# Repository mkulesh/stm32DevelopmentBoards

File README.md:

#  "Development boards and software templates for STM32 MCU"

This repository contains schematic of development boards, PCB, and C++ source code templates that can be helpful for development using STM32 micro-controllers. It provides small, universal, and breadboards-friendly adapter and development board for wide range of STM32 controllers.  There are three sets:

## STM32-Pi Board

The first board is a two-layers STM32F4 board, which have a form-factor of Raspberry Pi B+ that allows us to use any case available for this single-board computer:

If you like to test this board, you can order it [on DirtyPCBs.com](http://dirtypcbs.com/store/designer/details/9348/6105/stm32-pi-board-v1-3-zip)

### Specification
* It is based on high-performance ARM®Cortex®-M4 32-bit RISC micro-controller [STM32F405RG](http://www.st.com/en/microcontrollers/stm32f405rg.html)
* SMD HSE and LSE crystals
* Micro SD Card Connector
* Mini USB Type B Connector with USB EMI filtering and ESD protection. This connector can be used for data transfer and powering
* A separate +5V DC connector (1 mm X 3.2 mm) instead of Raspberry Pi audio jack
* 6-pin SWD connector used to program the MCU
* [ESP8266](https://en.wikipedia.org/wiki/ESP8266) WiFi Module ESP-11 instead of Raspberry Pi network connector
* 5-pin connector used to flash and program the ESP-11 module
* Breadboard-compatible 1x20-pin and 1x10-pin headers connected to free MCU pins
* Reset button
* One RGB LED
* Low power audio DAC with PLL UDA1334ATS
* 2x class-D mono audio power amplifier IS31AP2005 (2 x 2.95W) 
* 4 pads for audio output instead of Raspberry Pi USB connector
* SMD size for passive components is 0805

### Documentation
* [Отладочная плата STM32F4 в форм-факторе Raspberry Pi (In Russian)](https://habr.com/post/413101)
* [Schematic](https://docs.google.com/viewer?url=https://github.com/mkulesh/stm32DevelopmentBoards/raw/master/pcb/stm32_pi_board_sch.pdf) 
* [Dimensions](https://docs.google.com/viewer?url=https://github.com/mkulesh/stm32DevelopmentBoards/raw/master/pcb/stm32_pi_board_mech.pdf) 
* [Top layer](https://docs.google.com/viewer?url=https://github.com/mkulesh/stm32DevelopmentBoards/raw/master/pcb/stm32_pi_board_top.pdf)
* [Bottom layer](https://docs.google.com/viewer?url=https://github.com/mkulesh/stm32DevelopmentBoards/raw/master/pcb/stm32_pi_board_bottom.pdf) 
* [Bill of materials](http://htmlpreview.github.io/?https://github.com/mkulesh/stm32DevelopmentBoards/blob/master/pcb/stm32_pi_board_bom.html)
* The C++ example in the directory [src/PI405RG](https://github.com/mkulesh/stm32DevelopmentBoards/tree/master/src/PI405RG) demonstrates how to use RTC, SD Card with FatFS, and ESP-11 module.

## Universal STM32 Boards:

These developments boards are two-side breadboard adapters for LQFP32/48/64 IC's, equipment with adaptable power supply circuit, HSE and LSE crystal circuit, reset button, and a **custom** 10-pin JTAG connector. SMD size for passive components is 0805. 

The adapter between 20-pin JTAG and this custom connector is also included in the set:

You can order these boards [on DirtyPCBs.com](http://dirtypcbs.com/store/designer/details/9348/5771/stm32-development-boards)

## LQFP-Breadboard Adapters:

These boards are just one-side breadboard adapters for LQFP32/48/64 IC's:

You can order these boards [on DirtyPCBs.com](http://dirtypcbs.com/store/designer/details/9348/5770/lqfp-adapters-zip)

## Repository Content:

* The directory **pcb** contains schematic and board layout developed in [Eagle CAD](https://www.autodesk.com/products/eagle/free-download)
* In the directory **images**, you can find some photos of assembled boards
* The directory **src** contains test examples developed in [System Workbench for STM32](http://www.st.com/en/development-tools/sw4stm32.html). These test programs are based on HAL library and an object-oriented abstraction layer called *StmPlusPlus*. Currently, following chips are tested: STM32F303K8Tx, STM32F303RBTx, STM32F373CBTx, STM32F373CCTx, STM32F410RBTx,  STM32F405RGTx

## Reviews and Publications:
* [Discussion on www.mikrocontroller.net (In German)](https://www.mikrocontroller.net/topic/433910)
* [Нестандартный способ подружиться с STM32: не Ардуино и не Discovery (In Russian)](https://habr.com/post/406313)

## License
This software is published under the *GNU General Public License, Version 3*

Copyright (C) 2014-2017 Mikhail Kulesh

This program is free software: you can redistribute it and/or modify it under the terms of the GNU General Public License as published by the Free Software Foundation, either version 3 of the License, or (at your option) any later version.

This program is distributed in the hope that it will be useful, but WITHOUT ANY WARRANTY; without even the implied warranty of MERCHANTABILITY or FITNESS FOR A PARTICULAR PURPOSE.  See the GNU General Public License for more details. You should have received a copy of the GNU General Public License along with this program.

If not, see [www.gnu.org/licenses](http://www.gnu.org/licenses).

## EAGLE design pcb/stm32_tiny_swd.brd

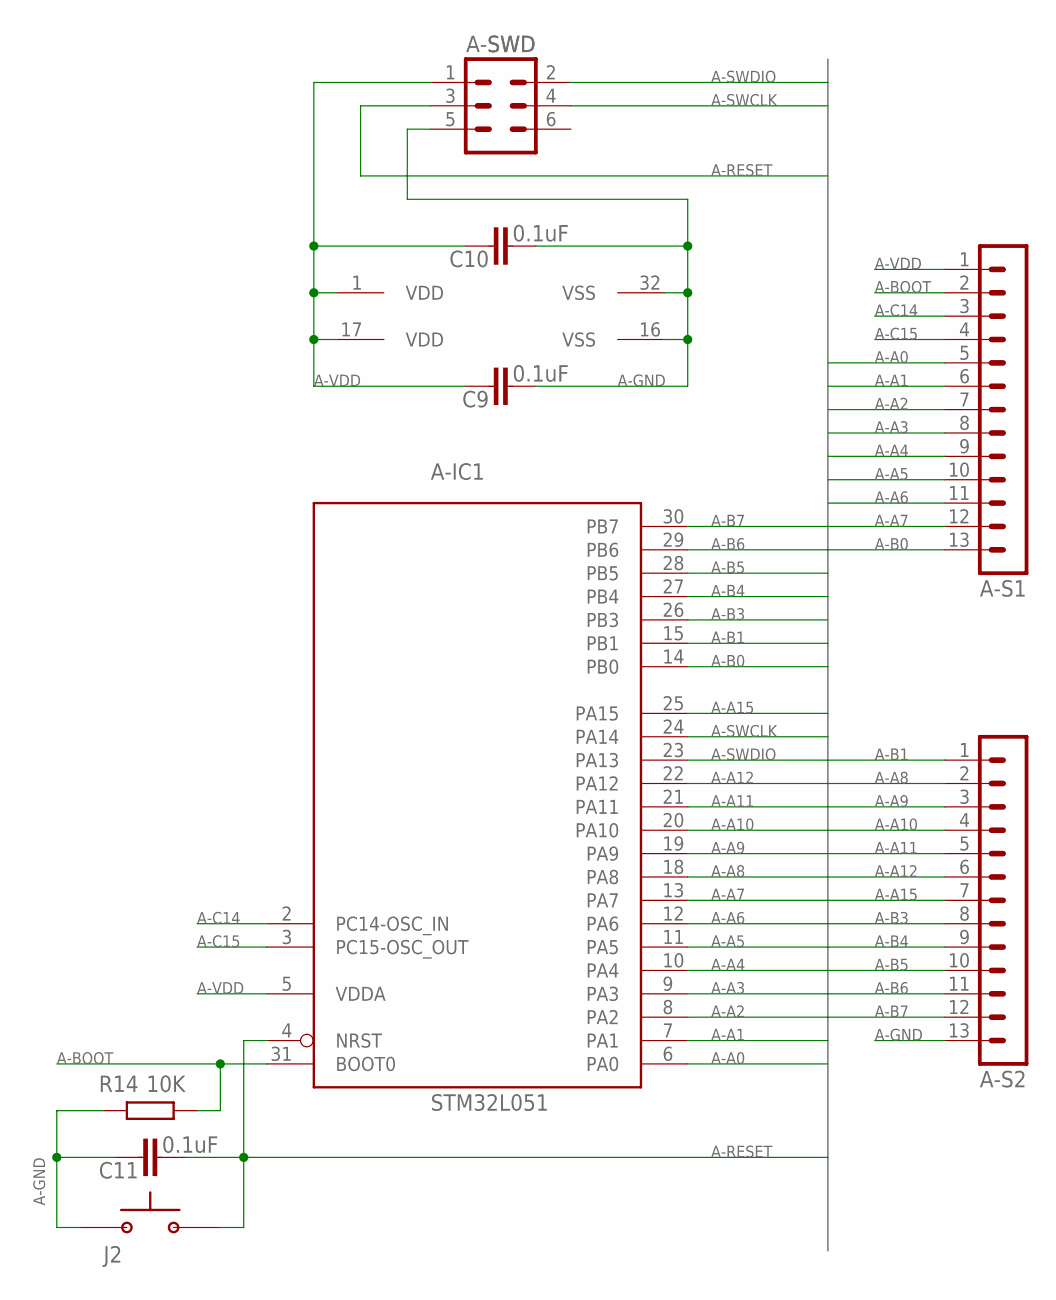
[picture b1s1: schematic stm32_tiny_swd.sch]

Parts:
A-IC1: STM32L051; LQFP32
A-S1, A-S2: MA13-1
A-SWD: SWD; MA03-2
C9, C10, C11: 0.1uF; C0805
J2: BUTTON-FSM14JRT
R14: 10K; R0805

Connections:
A-A0: A-IC1.6 (PA0), A-S1.5
A-A1: A-IC1.7 (PA1), A-S1.6
A-A2: A-IC1.8 (PA2), A-S1.7
A-A3: A-IC1.9 (PA3), A-S1.8
A-A4: A-IC1.10 (PA4), A-S1.9
A-A5: A-IC1.11 (PA5), A-S1.10
A-A6: A-IC1.12 (PA6), A-S1.11
A-A7: A-IC1.13 (PA7), A-S1.12
A-A8: A-IC1.18 (PA8), A-S2.2
A-A9: A-IC1.19 (PA9), A-S2.3
A-A10: A-IC1.20 (PA10), A-S2.4
A-A11: A-IC1.21 (PA11), A-S2.5
A-A12: A-IC1.22 (PA12), A-S2.6
A-A15: A-IC1.25 (PA15), A-S2.7
A-B0: A-IC1.14 (PB0), A-S1.13
A-B1: A-IC1.15 (PB1), A-S2.1
A-B3: A-IC1.26 (PB3), A-S2.8
A-B4: A-IC1.27 (PB4), A-S2.9
A-B5: A-IC1.28 (PB5), A-S2.10
A-B6: A-IC1.29 (PB6), A-S2.11
A-B7: A-IC1.30 (PB7), A-S2.12
A-BOOT: A-IC1.31 (BOOT0), A-S1.2, R14.1
A-C14: A-IC1.2 (PC14-OSC_IN), A-S1.3
A-C15: A-IC1.3 (PC15-OSC_OUT), A-S1.4
A-GND: A-IC1.16 (VSS), A-IC1.32 (VSS), A-S2.13, A-SWD.5, C9.2, C10.2, C11.1, J2.P$1 (1), R14.2
A-RESET: A-IC1.4 (NRST), A-SWD.3, C11.2, J2.P$2 (2)
A-SWCLK: A-IC1.24 (PA14), A-SWD.4
A-SWDIO: A-IC1.23 (PA13), A-SWD.2
A-VDD: A-IC1.1 (VDD), A-IC1.5 (VDDA), A-IC1.17 (VDD), A-S1.1, A-SWD.1, C9.1, C10.1

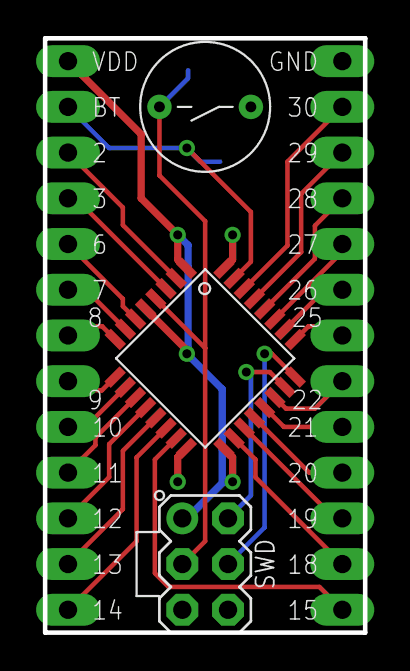
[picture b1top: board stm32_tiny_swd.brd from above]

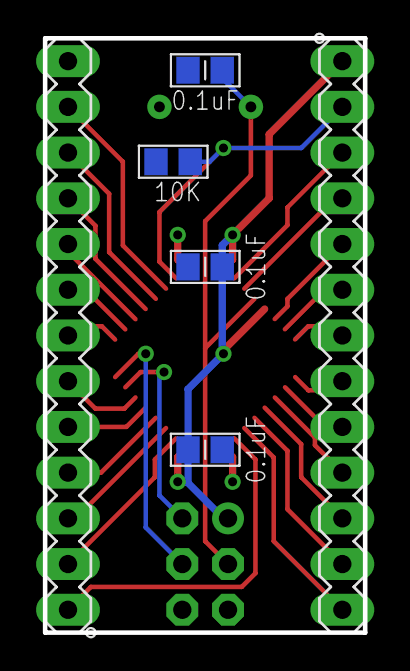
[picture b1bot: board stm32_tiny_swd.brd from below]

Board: 2 copper layers, 17.8 x 33.0 mm, 9 parts (6 on the bottom side), 29 nets.

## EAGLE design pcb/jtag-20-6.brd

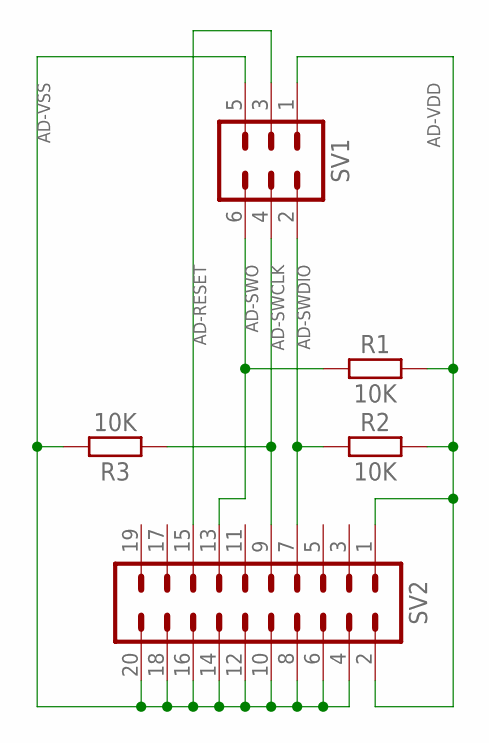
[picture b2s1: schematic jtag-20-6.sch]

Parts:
R1, R2, R3: 10K; R1206
SV1: MA03-2
SV2: MA10-2

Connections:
AD-RESET: SV1.3, SV2.15
AD-SWCLK: R3.1, SV1.4, SV2.9
AD-SWDIO: R2.1, SV1.2, SV2.7
AD-SWO: R1.1, SV1.6, SV2.13
AD-VDD: R1.2, R2.2, SV1.1, SV2.1, SV2.2
AD-VSS: R3.2, SV1.5, SV2.4, SV2.6, SV2.8, SV2.10, SV2.12, SV2.14, SV2.16, SV2.18, SV2.20

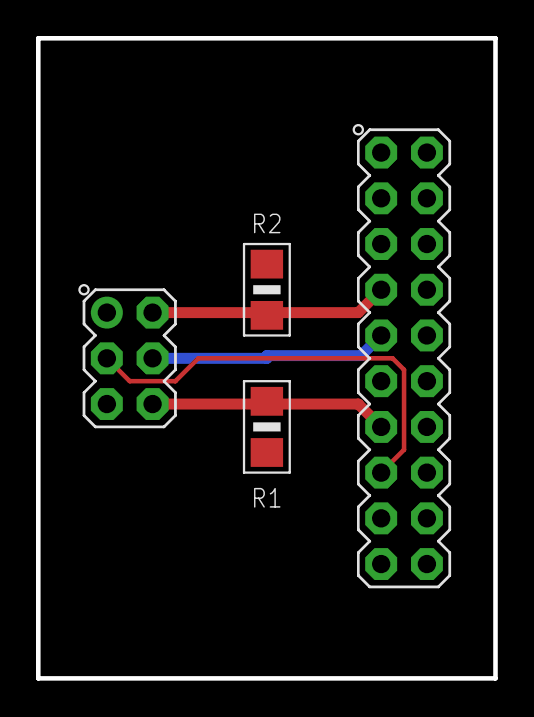
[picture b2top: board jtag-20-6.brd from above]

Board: 2 copper layers, 25.4 x 35.6 mm, 5 parts (1 on the bottom side), 6 nets.

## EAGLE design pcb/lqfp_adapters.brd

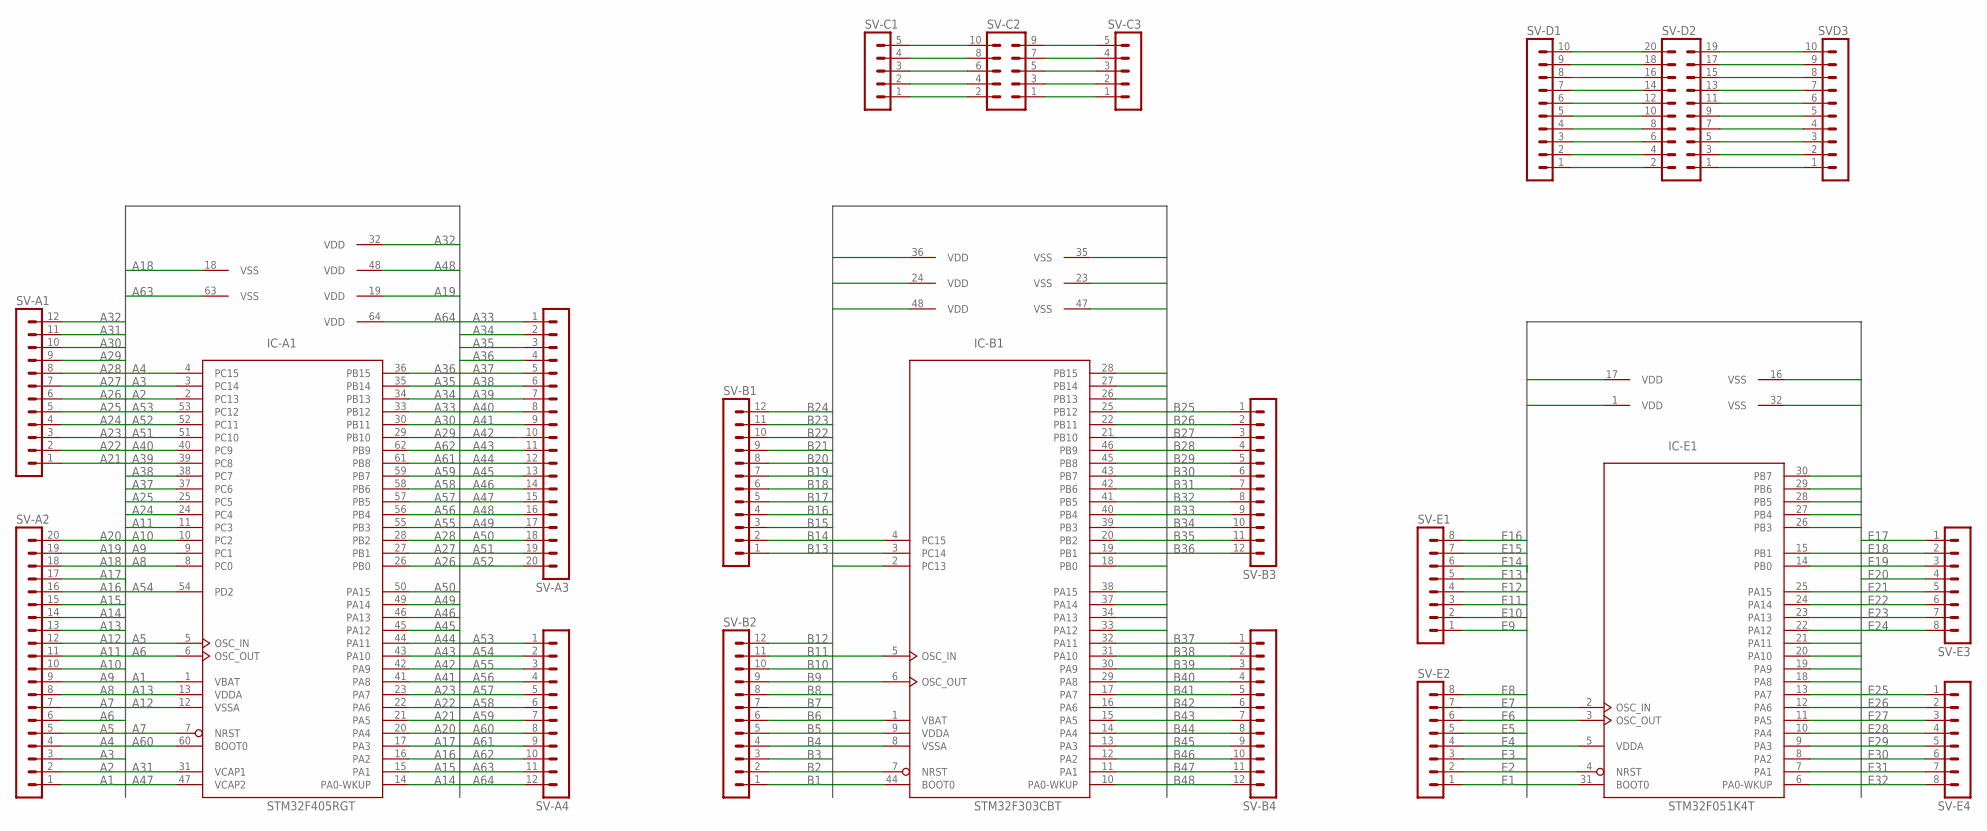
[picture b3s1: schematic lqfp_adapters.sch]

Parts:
IC-A1: STM32F405RGT; LQFP64
IC-B1: STM32F303CBT; LQFP48
IC-E1: STM32F051K4T; LQFP32
SV-A1, SV-A4: MA12-1NO-PL; MA12-1-NO-PL
SV-A2, SV-A3: MA20-1NO-PL; MA20-1-NO-PL
SV-B1, SV-B2, SV-B3, SV-B4: MA12-1NO-PL; MA12-1-NO-PL
SV-C1, SV-C3: MA05-1NO-PL; MA05-1-NO-PL
SV-C2: MA05-2
SV-D1: MA10-1NO-PL; MA10-1-NO-PL
SV-D2: MA10-2
SV-E1, SV-E2, SV-E3, SV-E4: MA08-1NO-PL; MA08-1-NO-PL
SVD3: MA10-1NO-PL; MA10-1-NO-PL

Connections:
A1: IC-A1.1 (VBAT), SV-A2.1
A2: IC-A1.2 (PC13), SV-A2.2
A3: IC-A1.3 (PC14), SV-A2.3
A4: IC-A1.4 (PC15), SV-A2.4
A5: IC-A1.5 (OSC_IN), SV-A2.5
A6: IC-A1.6 (OSC_OUT), SV-A2.6
A7: IC-A1.7 (NRST), SV-A2.7
A8: IC-A1.8 (PC0), SV-A2.8
A9: IC-A1.9 (PC1), SV-A2.9
A10: IC-A1.10 (PC2), SV-A2.10
A11: IC-A1.11 (PC3), SV-A2.11
A12: IC-A1.12 (VSSA), SV-A2.12
A13: IC-A1.13 (VDDA), SV-A2.13
A14: IC-A1.14 (PA0-WKUP), SV-A2.14
A15: IC-A1.15 (PA1), SV-A2.15
A16: IC-A1.16 (PA2), SV-A2.16
A17: IC-A1.17 (PA3), SV-A2.17
A18: IC-A1.18 (VSS), SV-A2.18
A19: IC-A1.19 (VDD), SV-A2.19
A20: IC-A1.20 (PA4), SV-A2.20
A21: IC-A1.21 (PA5), SV-A1.1
A22: IC-A1.22 (PA6), SV-A1.2
A23: IC-A1.23 (PA7), SV-A1.3
A24: IC-A1.24 (PC4), SV-A1.4
A25: IC-A1.25 (PC5), SV-A1.5
A26: IC-A1.26 (PB0), SV-A1.6
A27: IC-A1.27 (PB1), SV-A1.7
A28: IC-A1.28 (PB2), SV-A1.8
A29: IC-A1.29 (PB10), SV-A1.9
A30: IC-A1.30 (PB11), SV-A1.10
A31: IC-A1.31 (VCAP1), SV-A1.11
A32: IC-A1.32 (VDD), SV-A1.12
A33: IC-A1.33 (PB12), SV-A3.1
A34: IC-A1.34 (PB13), SV-A3.2
A35: IC-A1.35 (PB14), SV-A3.3
A36: IC-A1.36 (PB15), SV-A3.4
A37: IC-A1.37 (PC6), SV-A3.5
A38: IC-A1.38 (PC7), SV-A3.6
A39: IC-A1.39 (PC8), SV-A3.7
A40: IC-A1.40 (PC9), SV-A3.8
A41: IC-A1.41 (PA8), SV-A3.9
A42: IC-A1.42 (PA9), SV-A3.10
A43: IC-A1.43 (PA10), SV-A3.11
A44: IC-A1.44 (PA11), SV-A3.12
A45: IC-A1.45 (PA12), SV-A3.13
A46: IC-A1.46 (PA13), SV-A3.14
A47: IC-A1.47 (VCAP2), SV-A3.15
A48: IC-A1.48 (VDD), SV-A3.16
A49: IC-A1.49 (PA14), SV-A3.17
A50: IC-A1.50 (PA15), SV-A3.18
A51: IC-A1.51 (PC10), SV-A3.19
A52: IC-A1.52 (PC11), SV-A3.20
A53: IC-A1.53 (PC12), SV-A4.1
A54: IC-A1.54 (PD2), SV-A4.2
A55: IC-A1.55 (PB3), SV-A4.3
A56: IC-A1.56 (PB4), SV-A4.4
A57: IC-A1.57 (PB5), SV-A4.5
A58: IC-A1.58 (PB6), SV-A4.6
A59: IC-A1.59 (PB7), SV-A4.7
A60: IC-A1.60 (BOOT0), SV-A4.8
A61: IC-A1.61 (PB8), SV-A4.9
A62: IC-A1.62 (PB9), SV-A4.10
A63: IC-A1.63 (VSS), SV-A4.11
A64: IC-A1.64 (VDD), SV-A4.12
B1: IC-B1.1 (VBAT), SV-B2.1
B2: IC-B1.2 (PC13), SV-B2.2
B3: IC-B1.3 (PC14), SV-B2.3
B4: IC-B1.4 (PC15), SV-B2.4
B5: IC-B1.5 (OSC_IN), SV-B2.5
B6: IC-B1.6 (OSC_OUT), SV-B2.6
B7: IC-B1.7 (NRST), SV-B2.7
B8: IC-B1.8 (VSSA), SV-B2.8
B9: IC-B1.9 (VDDA), SV-B2.9
B10: IC-B1.10 (PA0-WKUP), SV-B2.10
B11: IC-B1.11 (PA1), SV-B2.11
B12: IC-B1.12 (PA2), SV-B2.12
B13: IC-B1.13 (PA3), SV-B1.1
B14: IC-B1.14 (PA4), SV-B1.2
B15: IC-B1.15 (PA5), SV-B1.3
B16: IC-B1.16 (PA6), SV-B1.4
B17: IC-B1.17 (PA7), SV-B1.5
B18: IC-B1.18 (PB0), SV-B1.6
B19: IC-B1.19 (PB1), SV-B1.7
B20: IC-B1.20 (PB2), SV-B1.8
B21: IC-B1.21 (PB10), SV-B1.9
B22: IC-B1.22 (PB11), SV-B1.10
B23: IC-B1.23 (VSS), SV-B1.11
B24: IC-B1.24 (VDD), SV-B1.12
B25: IC-B1.25 (PB12), SV-B3.1
B26: IC-B1.26 (PB13), SV-B3.2
B27: IC-B1.27 (PB14), SV-B3.3
B28: IC-B1.28 (PB15), SV-B3.4
B29: IC-B1.29 (PA8), SV-B3.5
B30: IC-B1.30 (PA9), SV-B3.6
B31: IC-B1.31 (PA10), SV-B3.7
B32: IC-B1.32 (PA11), SV-B3.8
B33: IC-B1.33 (PA12), SV-B3.9
B34: IC-B1.34 (PA13), SV-B3.10
B35: IC-B1.35 (VSS), SV-B3.11
B36: IC-B1.36 (VDD), SV-B3.12
B37: IC-B1.37 (PA14), SV-B4.1
B38: IC-B1.38 (PA15), SV-B4.2
B39: IC-B1.39 (PB3), SV-B4.3
B40: IC-B1.40 (PB4), SV-B4.4
B41: IC-B1.41 (PB5), SV-B4.5
B42: IC-B1.42 (PB6), SV-B4.6
B43: IC-B1.43 (PB7), SV-B4.7
B44: IC-B1.44 (BOOT0), SV-B4.8
B45: IC-B1.45 (PB8), SV-B4.9
B46: IC-B1.46 (PB9), SV-B4.10
B47: IC-B1.47 (VSS), SV-B4.11
B48: IC-B1.48 (VDD), SV-B4.12
E1: IC-E1.1 (VDD), SV-E2.1
E2: IC-E1.2 (OSC_IN), SV-E2.2
E3: IC-E1.3 (OSC_OUT), SV-E2.3
E4: IC-E1.4 (NRST), SV-E2.4
E5: IC-E1.5 (VDDA), SV-E2.5
E6: IC-E1.6 (PA0-WKUP), SV-E2.6
E7: IC-E1.7 (PA1), SV-E2.7
E8: IC-E1.8 (PA2), SV-E2.8
E9: IC-E1.9 (PA3), SV-E1.1
E10: IC-E1.10 (PA4), SV-E1.2
E11: IC-E1.11 (PA5), SV-E1.3
E12: IC-E1.12 (PA6), SV-E1.4
E13: IC-E1.13 (PA7), SV-E1.5
E14: IC-E1.14 (PB0), SV-E1.6
E15: IC-E1.15 (PB1), SV-E1.7
E16: IC-E1.16 (VSS), SV-E1.8
E17: IC-E1.17 (VDD), SV-E3.1
E18: IC-E1.18 (PA8), SV-E3.2
E19: IC-E1.19 (PA9), SV-E3.3
E20: IC-E1.20 (PA10), SV-E3.4
E21: IC-E1.21 (PA11), SV-E3.5
E22: IC-E1.22 (PA12), SV-E3.6
E23: IC-E1.23 (PA13), SV-E3.7
E24: IC-E1.24 (PA14), SV-E3.8
E25: IC-E1.25 (PA15), SV-E4.1
E26: IC-E1.26 (PB3), SV-E4.2
E27: IC-E1.27 (PB4), SV-E4.3
E28: IC-E1.28 (PB5), SV-E4.4
E29: IC-E1.29 (PB6), SV-E4.5
E30: IC-E1.30 (PB7), SV-E4.6
E31: IC-E1.31 (BOOT0), SV-E4.7
E32: IC-E1.32 (VSS), SV-E4.8
unnamed: SV-C2.1, SV-C3.1
unnamed: SV-C2.3, SV-C3.2
unnamed: SV-C2.5, SV-C3.3
unnamed: SV-C2.7, SV-C3.4
unnamed: SV-C2.9, SV-C3.5
unnamed: SV-C1.1, SV-C2.2
unnamed: SV-C1.2, SV-C2.4
unnamed: SV-C1.3, SV-C2.6
unnamed: SV-C1.4, SV-C2.8
unnamed: SV-C1.5, SV-C2.10
unnamed: SV-D2.1, SVD3.1
unnamed: SV-D2.3, SVD3.2
unnamed: SV-D2.5, SVD3.3
unnamed: SV-D2.7, SVD3.4
unnamed: SV-D2.9, SVD3.5
unnamed: SV-D2.11, SVD3.6
unnamed: SV-D2.13, SVD3.7
unnamed: SV-D2.15, SVD3.8
unnamed: SV-D2.17, SVD3.9
unnamed: SV-D2.19, SVD3.10
unnamed: SV-D1.10, SV-D2.20
unnamed: SV-D1.9, SV-D2.18
unnamed: SV-D1.8, SV-D2.16
unnamed: SV-D1.7, SV-D2.14
unnamed: SV-D1.6, SV-D2.12
unnamed: SV-D1.5, SV-D2.10
unnamed: SV-D1.4, SV-D2.8
unnamed: SV-D1.3, SV-D2.6
unnamed: SV-D1.2, SV-D2.4
unnamed: SV-D1.1, SV-D2.2

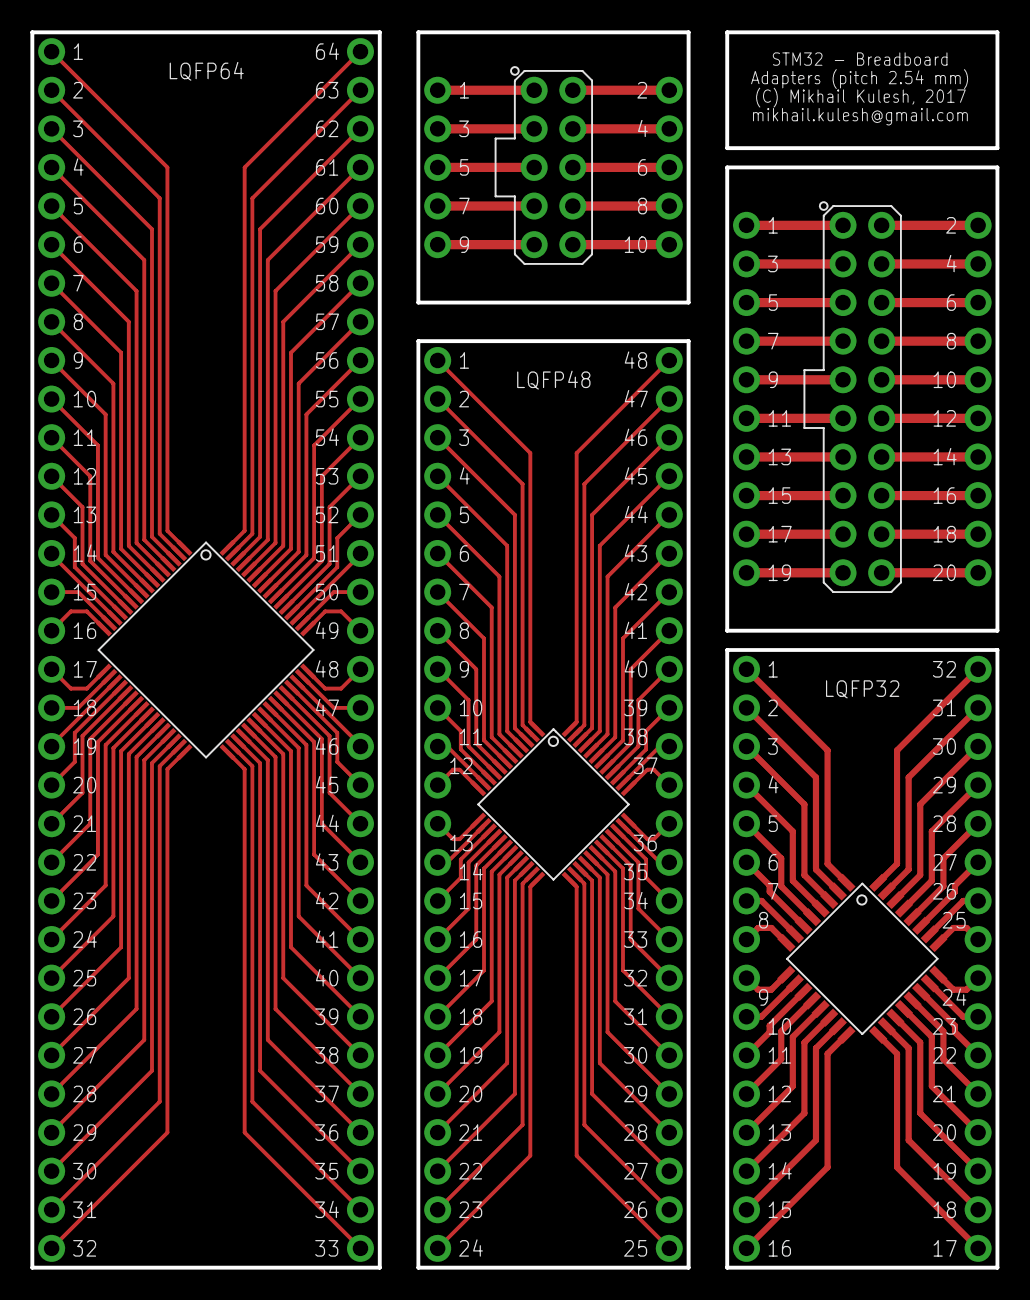
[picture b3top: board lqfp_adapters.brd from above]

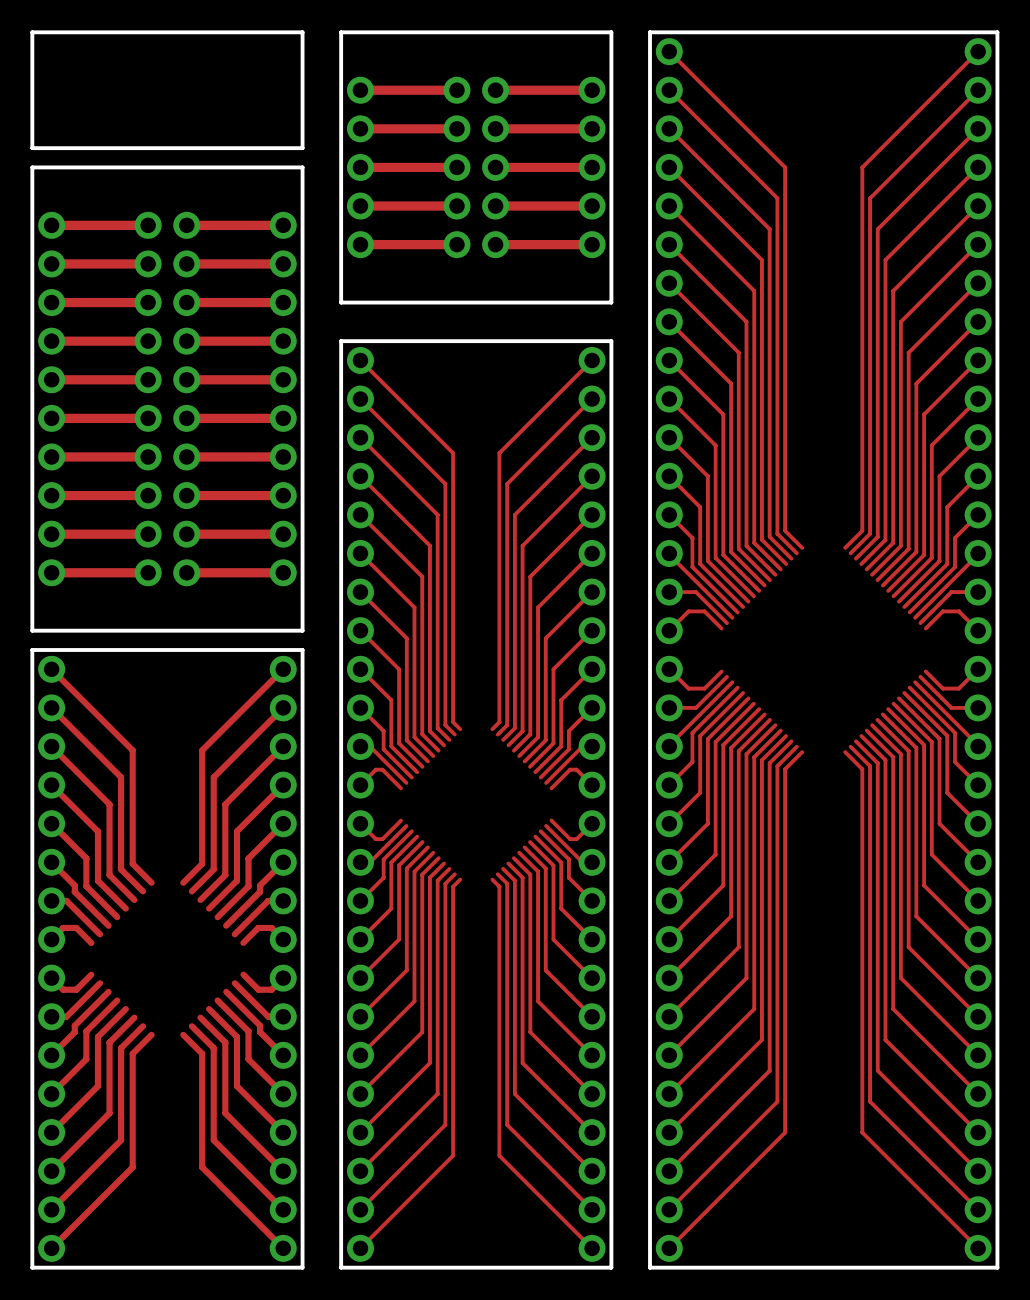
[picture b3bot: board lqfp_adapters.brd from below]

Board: 2 copper layers, 63.5 x 81.3 mm, 21 parts (16 on the bottom side), 174 nets.

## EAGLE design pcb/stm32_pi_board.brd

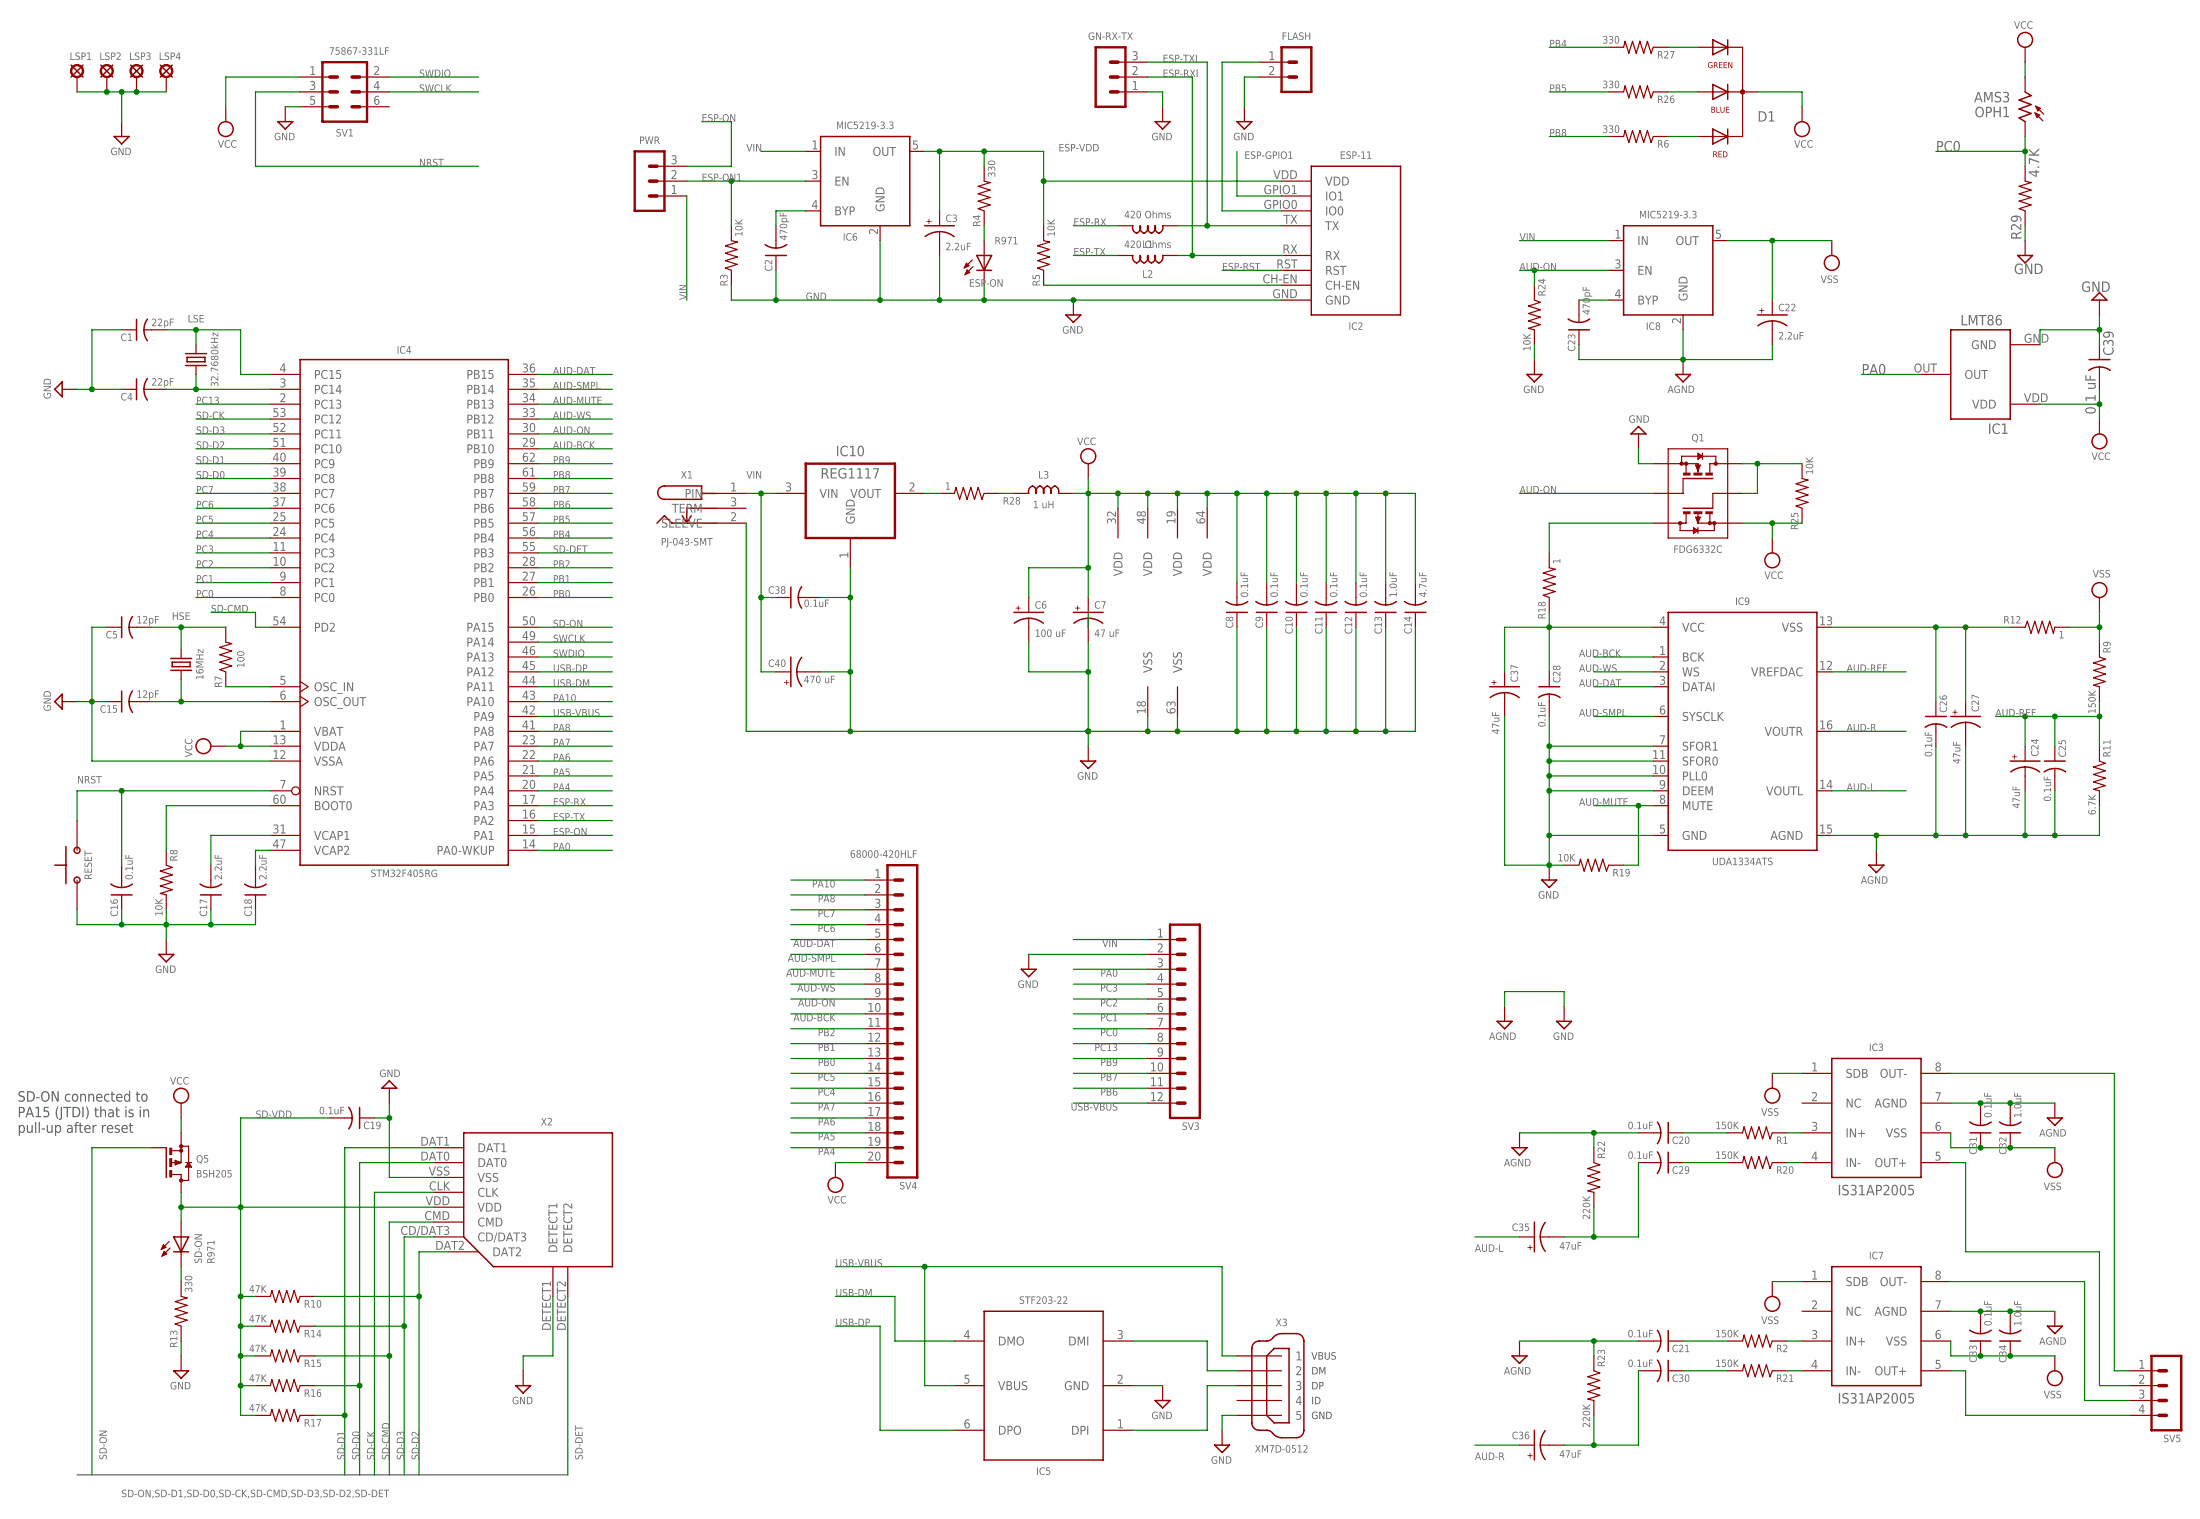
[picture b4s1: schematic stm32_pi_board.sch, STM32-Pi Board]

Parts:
C1, C4: 22pF; C0805
C2, C23: 470pF; C0805
C3, C22: 2.2uF; CPOL0805
C5, C15: 12pF; C0805
C6: 100 uF; CPOL1311
C7: 47 uF; CPOL0805
C8, C9, C10, C11, C12, C16, C19, C20, C21, C25, C26, C28, C29, C30, C31, C33, C38: 0.1uF; C0805
C13, C32, C34: 1.0uF; C0805
C14: 4.7uF; C0805
C17, C18: 2.2uF; C0805
C24, C27, C35, C36, C37: 47uF; CPOL1311
C39: 0.1 uF; C0805
C40: 470 uF; CPOL2917
D1: RGB-LED3X1MM; RGB-LED-SMD-3X1
ESP-ON: R971; CHIP-LED0805
FLASH: MA02-1
GN-RX-TX: MA03-1PL; MA03-1
HSE: 16MHz; Q-HC-46X
IC1: LMT86
IC2: ESP-11
IC3, IC7: IS31AP2005; MSOP-8
IC4: STM32F405RG; LQFP64
IC5: STF203-22; SC70-6
IC6, IC8: MIC5219-3.3; SOT23-5
IC9: UDA1334ATS; SSOP16
IC10: REG1117; SOT223
L1, L2: 420 Ohms; L0603
L3: 1 uH; L0805
LSE: 32.7680kHz; Q-CM7V-T1A
LSP1, LSP2, LSP3, LSP4: LSP27
OPH1: AMS3; VT900
PWR: MA03-1PL; MA03-1
Q1: FDG6332C; SC70-6
Q5: BSH205; SOT23
R1, R2, R9, R20, R21: 150K; R0805
R3, R5, R8, R19, R24, R25: 10K; R0805
R4, R6, R13, R26, R27: 330; R0805
R7: 100; R0805
R10, R14, R15, R16, R17: 47K; R0805
R11: 6.7K; R0805
R12, R18, R28: 1; R0805
R22, R23: 220K; R0805
R29: 4.7K; R0805
RESET: BUTTON-FSM14JRT
SD-ON: R971; CHIP-LED0805
SV1: 75867-331LF; MA03-2
SV3: MA12-1NO-PL; MA12-1-NO-PL
SV4: 68000-420HLF; MA20-1-NO-PL
SV5: MA04-1PL; MA04-1
X1: PJ-043-SMT; BUCHSE-1.0X3.2
X2: DM3AT
X3: XM7D-0512

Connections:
AUD-BCK: IC4.29 (PB10), IC9.1 (BCK), SV4.10
AUD-DAT: IC4.36 (PB15), IC9.3 (DATAI), SV4.5
AUD-L: C35.1+ (+), IC9.14 (VOUTL)
AUD-MUTE: IC4.34 (PB13), IC9.8 (MUTE), R19.1, SV4.7
AUD-ON: IC4.30 (PB11), IC8.3 (EN), Q1.2, R24.1, SV4.9
AUD-R: C36.1+ (+), IC9.16 (VOUTR)
AUD-REF: C24.1+ (+), C25.1, IC9.12 (VREFDAC), R9.2, R11.1
AUD-SMPL: IC4.35 (PB14), IC9.6 (SYSCLK), SV4.6
AUD-WS: IC4.33 (PB12), IC9.2 (WS), SV4.8
BOOT: IC4.60 (BOOT0), R8.1
ESP-GPIO1: IC2.GPIO1 (IO1)
ESP-IO0: FLASH.1, IC2.GPIO0 (IO0)
ESP-ON: IC4.15 (PA1), PWR.3
ESP-ON1: IC6.3 (EN), PWR.2, R3.2
ESP-RST: IC2.RST
ESP-RX: IC4.17 (PA3), L1.2
ESP-RXI: GN-RX-TX.2, IC2.RX, L2.1
ESP-TX: IC4.16 (PA2), L2.2
ESP-TXI: GN-RX-TX.3, IC2.TX, L1.1
ESP-VDD: C3.1+ (+), IC2.VDD, IC6.5 (OUT), R4.2, R5.2
GND: C1.1, C2.1, C3.2- (-), C4.1, C5.1, C6.2- (-), C7.2- (-), C8.1, C9.1, C10.1, C11.1, C12.1, C13.1, C14.1, C15.1, C16.1, C17.1, C18.1, C19.1, C20.2, C21.2, C22.2- (-), C23.1, C24.2- (-), C25.2, C26.2, C27.2- (-), C28.2, C31.2, C32.2, C33.2, C34.2, C37.2- (-), C38.2, C39.1, C40.-, ESP-ON.C, FLASH.2, GN-RX-TX.1, IC1.GND, IC2.GND, IC3.7 (AGND), IC4.12 (VSSA), IC4.18 (VSS), IC4.63 (VSS), IC5.2 (GND), IC6.2 (GND), IC7.7 (AGND), IC8.2 (GND), IC9.5 (GND), IC9.7 (SFOR1), IC9.9 (DEEM), IC9.10 (PLL0), IC9.11 (SFOR0), IC9.15 (AGND), IC10.1 (GND), LSP1.MP, LSP2.MP, LSP3.MP, LSP4.MP, Q1.1, R3.1, R8.2, R11.2, R13.1, R19.2, R22.1, R23.1, R24.2, R29.1, RESET.P$1 (1), SV1.5, SV3.2, X1.2 (SLEEVE), X2.DETECT1, X2.VSS, X3.5
unnamed: C2.2, IC6.4 (BYP)
unnamed: D1.P$1 (AR), R6.1
unnamed: IC4.5 (OSC_IN), R7.1
unnamed: ESP-ON.A, R4.1
unnamed: IC3.8 (OUT-), SV5.1
unnamed: IC3.5 (OUT+), SV5.2
unnamed: C20.1, R1.2
unnamed: IC7.8 (OUT-), SV5.3
unnamed: IC7.5 (OUT+), SV5.4
unnamed: IC3.3 (IN+), R1.1
unnamed: IC7.3 (IN+), R2.1
unnamed: IC5.1 (DPI), X3.3
unnamed: IC5.3 (DMI), X3.2
unnamed: C21.1, R2.2
unnamed: IC3.4 (IN-), R20.1
unnamed: D1.P$4 (AB), R26.1
unnamed: C28.1, C37.1+ (+), IC9.4 (VCC), R18.1
unnamed: IC7.4 (IN-), R21.1
unnamed: C23.2, IC8.4 (BYP)
unnamed: C26.1, C27.1+ (+), IC9.13 (VSS), R12.1
unnamed: C30.1, R21.2
unnamed: IC2.CH-EN, R5.1
unnamed: C29.1, R20.2
unnamed: C29.2, C35.2- (-), R22.2
unnamed: Q1.3, R18.2
unnamed: C5.2, HSE.1, R7.2
unnamed: C30.2, C36.2- (-), R23.2
unnamed: D1.P$3 (AG), R27.1
unnamed: C15.2, HSE.2, IC4.6 (OSC_OUT)
unnamed: IC10.2 (VOUT), R28.2
unnamed: Q1.5, Q1.6, R25.2
unnamed: L3.1, R28.1
unnamed: R13.2, SD-ON.C
NRST: C16.2, IC4.7 (NRST), RESET.P$2 (2), SV1.3
PA0: IC1.OUT, IC4.14 (PA0-WKUP), SV3.3
PA4: IC4.20 (PA4), SV4.19
PA5: IC4.21 (PA5), SV4.18
PA6: IC4.22 (PA6), SV4.17
PA7: IC4.23 (PA7), SV4.16
PA8: IC4.41 (PA8), SV4.2
PA10: IC4.43 (PA10), SV4.1
PB0: IC4.26 (PB0), SV4.13
PB1: IC4.27 (PB1), SV4.12
PB2: IC4.28 (PB2), SV4.11
PB4: IC4.56 (PB4), R27.2
PB5: IC4.57 (PB5), R26.2
PB6: IC4.58 (PB6), SV3.11
PB7: IC4.59 (PB7), SV3.10
PB8: IC4.61 (PB8), R6.2
PB9: IC4.62 (PB9), SV3.9
PC0: IC4.8 (PC0), OPH1.1, R29.2, SV3.7
PC1: IC4.9 (PC1), SV3.6
PC2: IC4.10 (PC2), SV3.5
PC3: IC4.11 (PC3), SV3.4
PC4: IC4.24 (PC4), SV4.15
PC5: IC4.25 (PC5), SV4.14
PC6: IC4.37 (PC6), SV4.4
PC7: IC4.38 (PC7), SV4.3
PC13: IC4.2 (PC13), SV3.8
Q2M: C4.2, IC4.3 (PC14), LSE.1
Q2P: C1.2, IC4.4 (PC15), LSE.2
SD-CK: IC4.53 (PC12), X2.CLK
SD-CMD: IC4.54 (PD2), R15.1, X2.CMD
SD-D0: IC4.39 (PC8), R16.1, X2.DAT0
SD-D1: IC4.40 (PC9), R17.1, X2.DAT1
SD-D2: IC4.51 (PC10), R10.1, X2.DAT2
SD-D3: IC4.52 (PC11), R14.1, X2.CD/DAT3
SD-DET: IC4.55 (PB3), X2.DETECT2
SD-ON: IC4.50 (PA15), Q5.1 (G)
SD-VDD: C19.2, Q5.3 (D), R10.2, R14.2, R15.2, R16.2, R17.2, SD-ON.A, X2.VDD
SWCLK: IC4.49 (PA14), SV1.4
SWDIO: IC4.46 (PA13), SV1.2
USB-DM: IC4.44 (PA11), IC5.4 (DMO)
USB-DP: IC4.45 (PA12), IC5.6 (DPO)
USB-VBUS: IC4.42 (PA9), IC5.5 (VBUS), SV3.12, X3.1
VCAP3: C18.2, IC4.47 (VCAP2)
VCAP4: C17.2, IC4.31 (VCAP1)
VDD: C6.1+ (+), C7.1+ (+), C8.2, C9.2, C10.2, C11.2, C12.2, C13.2, C14.2, C39.2, D1.P$2 (C), IC1.VDD, IC4.1 (VBAT), IC4.13 (VDDA), IC4.19 (VDD), IC4.32 (VDD), IC4.48 (VDD), IC4.64 (VDD), L3.2, OPH1.2, Q1.4, Q5.2 (S), R25.1, SV1.1, SV4.20
VIN: C38.1, C40.+, IC6.1 (IN), IC8.1 (IN), IC10.3 (VIN), PWR.1, SV3.1, X1.1 (PIN)
VSS: C22.1+ (+), C31.1, C32.1, C33.1, C34.1, IC3.1 (SDB), IC3.6 (VSS), IC7.1 (SDB), IC7.6 (VSS), IC8.5 (OUT), R9.1, R12.2

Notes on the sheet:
SD-ON connected to PA15 (JTDI) that is in pull-up after reset

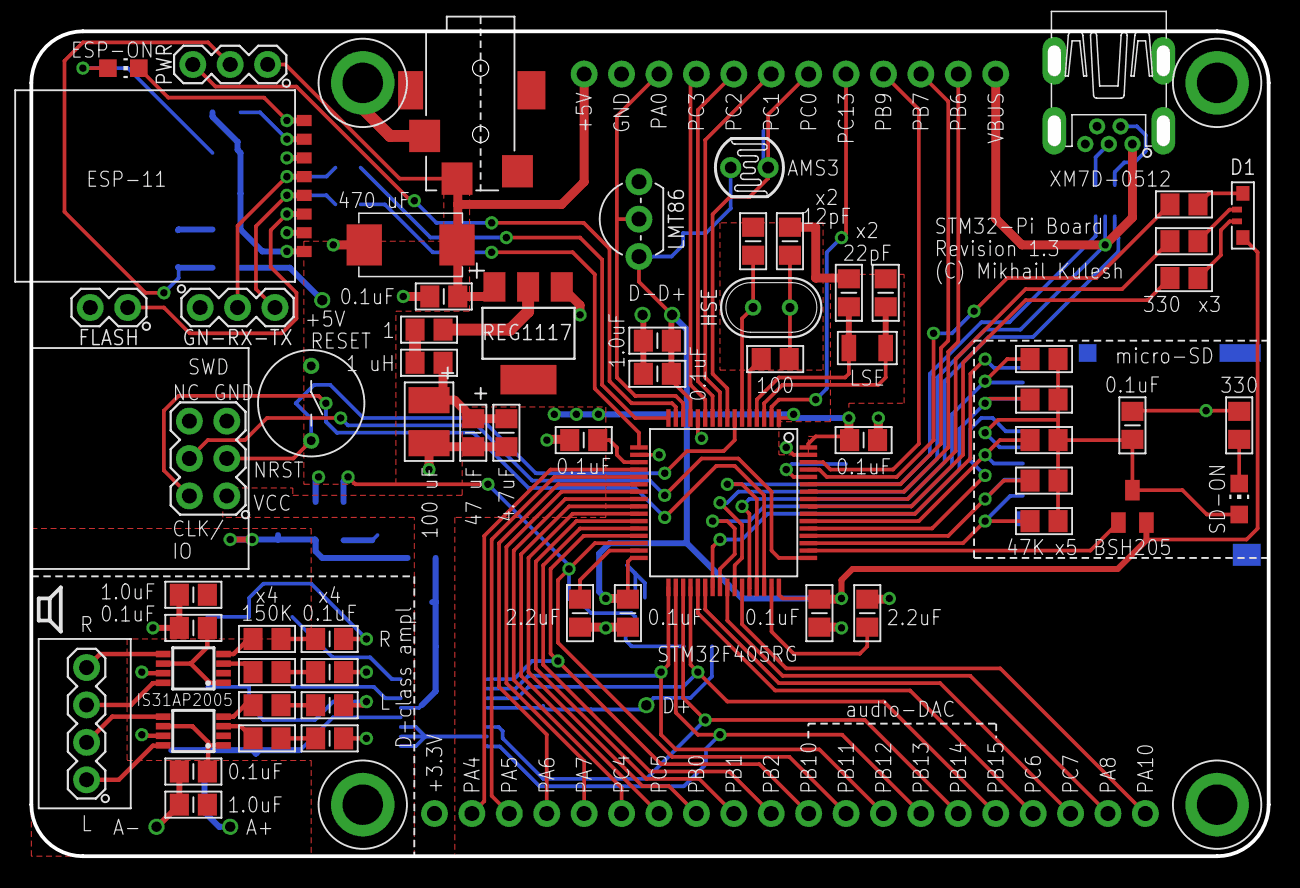
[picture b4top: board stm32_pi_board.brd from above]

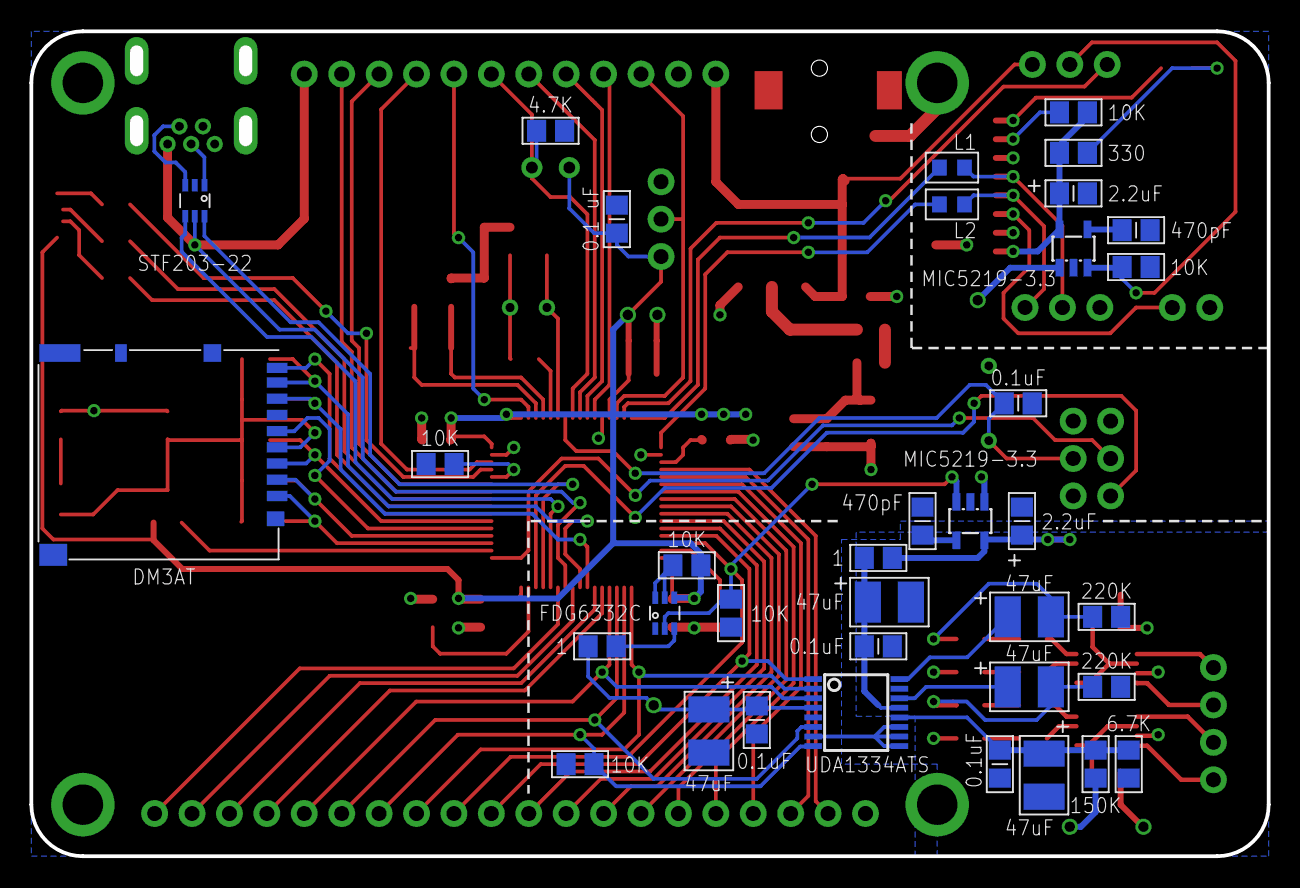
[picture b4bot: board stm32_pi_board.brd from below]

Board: 2 copper layers, 83.4 x 55.4 mm, 105 parts (36 on the bottom side), 99 nets.

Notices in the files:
README.md:
License: GNU GPLv3
